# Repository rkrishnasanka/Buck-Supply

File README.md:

# Buck Supply

## Buck Design Parameters

| Parameter             | Value |
|-----------------------|-------|
| Buck Inductor         | TBD   |
| Bootstrap Capacitance | TBD   |
| Buck Capacitor        | TBD   |

- Maximum input voltage is determined by the VCC for the NE555 and the IRS2004.
- The Bootstrap Capacitor has to have a small value to allow for a quick charge.
- The Buck Capacitor has to be large enough to absorb the entire voltage ripple at the output.

## Amplifier Design Parameters

- The amplifier gain (hence the magnitude of the error) is determined by the values of R1, R2, R3, R4.
- The gain should be such that the input to the comparator is good.

## Current Source Design Parameters

- By adjusting the R1, R2, RE we can adjust the value of the current source.
- Use the resources to figure out how to design the current source.

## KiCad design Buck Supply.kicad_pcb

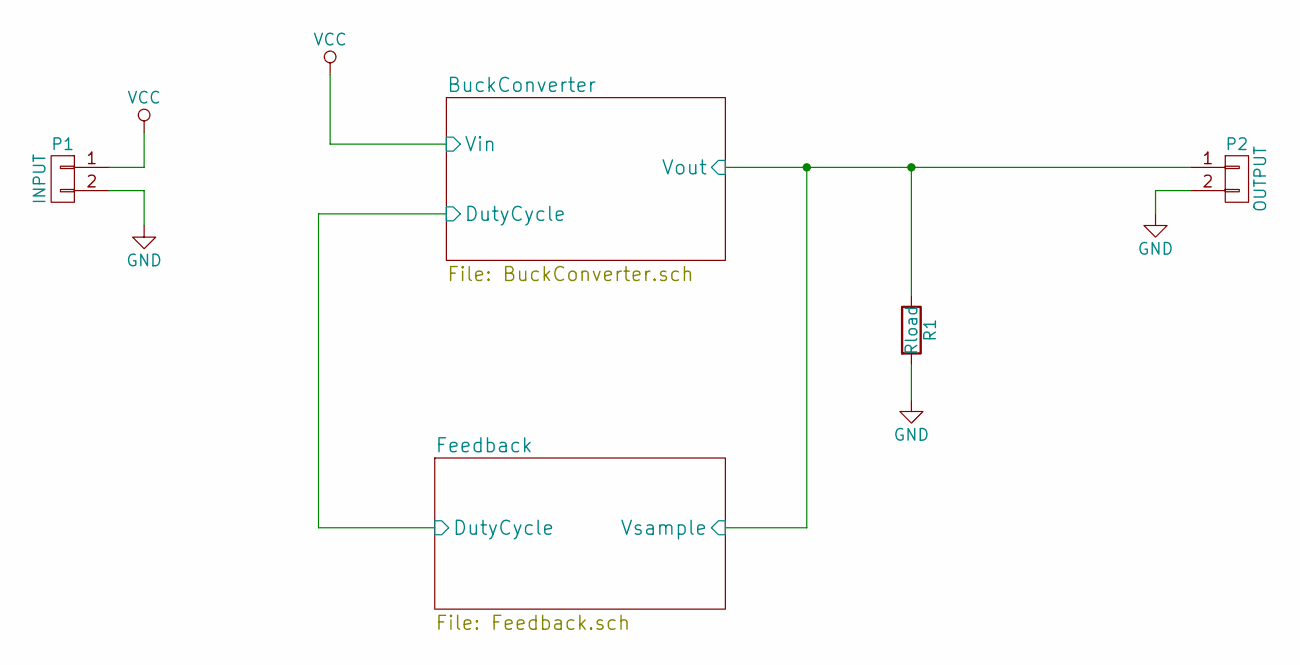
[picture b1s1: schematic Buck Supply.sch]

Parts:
P1: INPUT; Banana_Jack_2Pin
P2: OUTPUT; Banana_Jack_2Pin
R1: Rload; Resistor_Horizontal_RM30mm

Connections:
/BuckConverter/Vout: P2.1, R1.1; also elsewhere on the board
GND: P1.2, P2.2, R1.2; also elsewhere on the board
VCC: P1.1; also elsewhere on the board

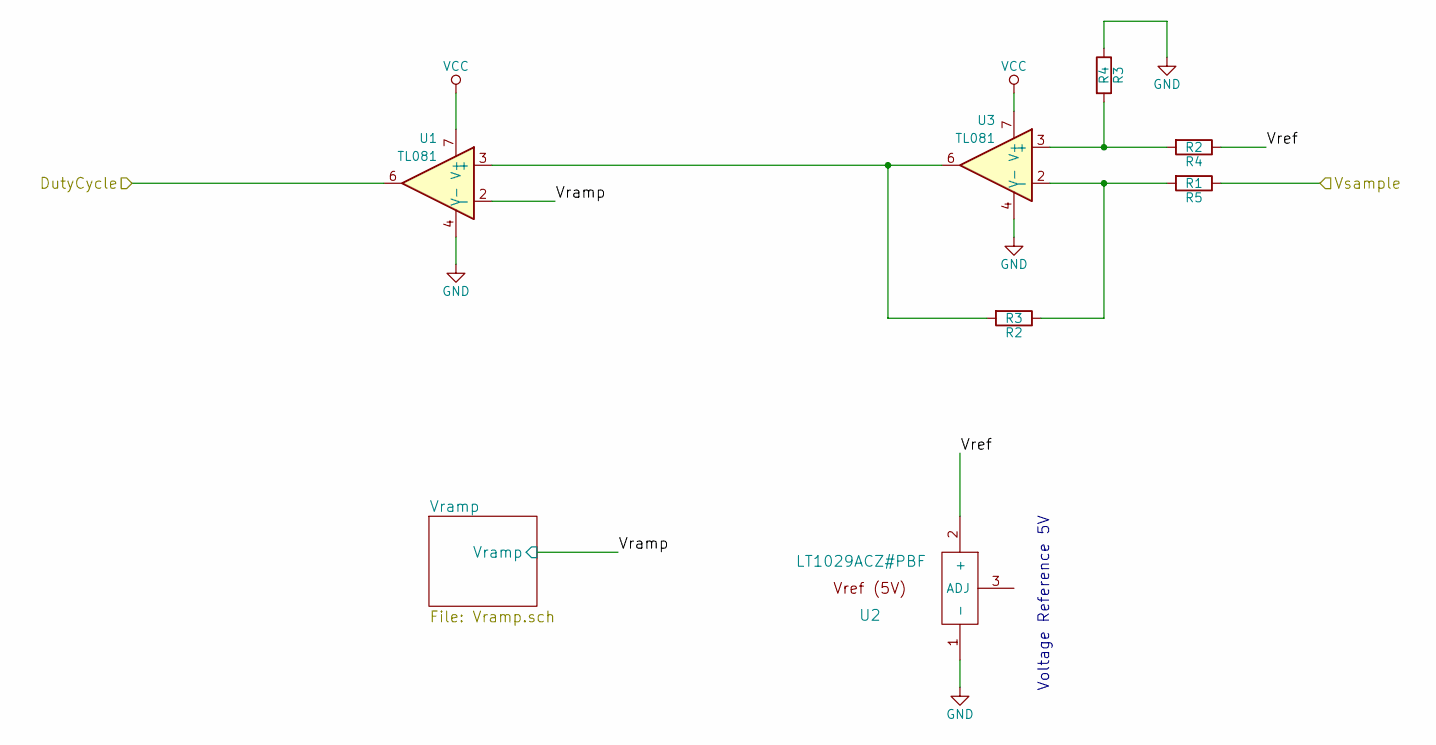
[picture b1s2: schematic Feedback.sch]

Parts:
R2: R3; Resistor_Horizontal_RM7mm
R3: R4; Resistor_Horizontal_RM7mm
R4: R2; Resistor_Horizontal_RM7mm
R5: R1; Resistor_Horizontal_RM7mm
U1, U3: TL081; DIP-8_W7.62mm_LongPads
U2: LT1029ACZ#PBF; TO-92_Inline_Wide

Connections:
/BuckConverter/DutyCycle: U1.6; also elsewhere on the board
/BuckConverter/Vout: R5.1; also elsewhere on the board
/Feedback/Vramp: U1.2 (-); also elsewhere on the board
/Feedback/Vref: R4.1, U2.2 (+)
GND: R3.1, U1.4 (V-), U2.1 (-), U3.4 (V-); also elsewhere on the board
unnamed: R2.1, R5.2, U3.2 (-)
unnamed: R2.2, U1.3 (+), U3.6
unnamed: R3.2, R4.2, U3.3 (+)
VCC: U1.7 (V+), U3.7 (V+); also elsewhere on the board

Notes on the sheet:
Voltage Reference 5V

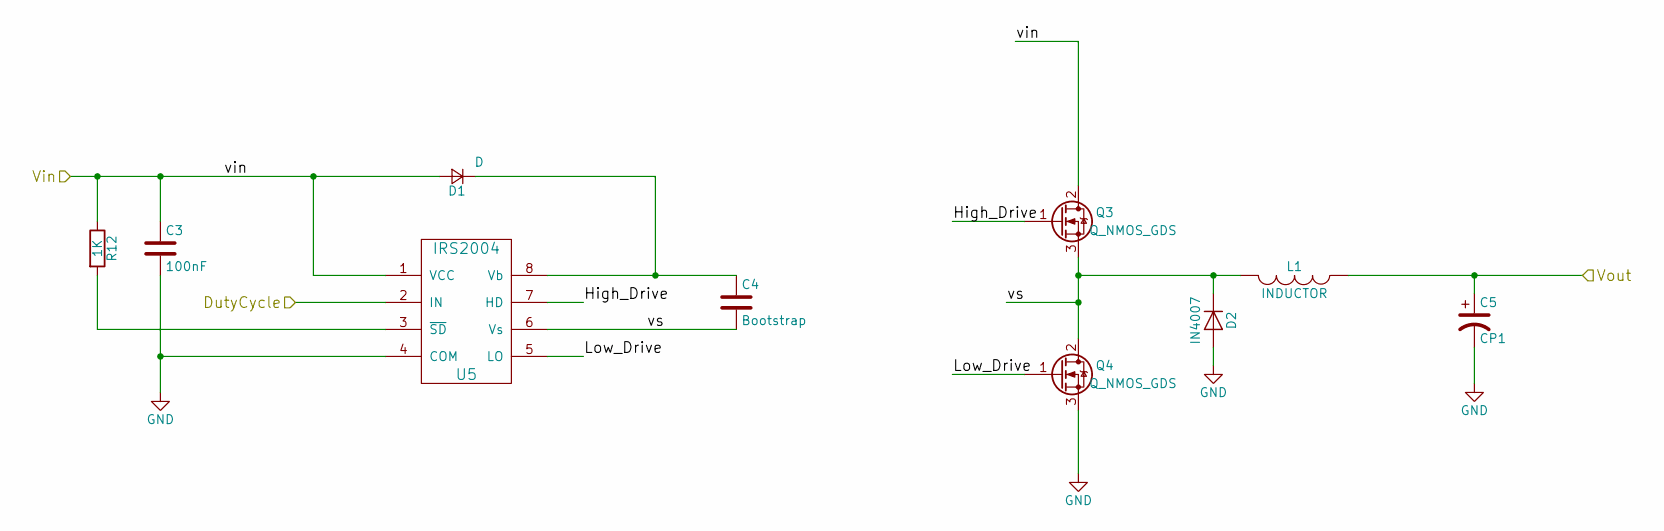
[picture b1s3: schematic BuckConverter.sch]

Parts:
C3: 100nF; C_Disc_D3_P2.5
C4: Bootstrap; C_Disc_D3_P2.5
C5: CP1; C_Radial_D16_L30_P7.5
D1: D; Diode_DO-35_SOD27_Horizontal_RM10
D2: IN4007; Diode_DO-41_SOD81_Horizontal_RM10
L1: INDUCTOR; Neosid_Inductor_Sd75
Q3, Q4: Q_NMOS_GDS; TO-220_Neutral123_Horizontal
R12: 1K; Resistor_Horizontal_RM7mm
U5: IRS2004; DIP-8_W7.62mm_LongPads

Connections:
/BuckConverter/DutyCycle: U5.2 (IN); also elsewhere on the board
/BuckConverter/High_Drive: Q3.1 (G), U5.7 (HD)
/BuckConverter/Low_Drive: Q4.1 (G), U5.5 (LO)
/BuckConverter/Vout: C5.1, L1.1; also elsewhere on the board
/BuckConverter/vs: C4.2, D2.1 (K), L1.2, Q3.3 (S), Q4.2 (D), U5.6 (Vs)
GND: C3.2, C5.2, D2.2 (A), Q4.3 (S), U5.4 (COM); also elsewhere on the board
unnamed: C4.1, D1.1 (K), U5.8 (Vb)
unnamed: R12.2, U5.3 (~SD)
VCC: C3.1, D1.2 (A), Q3.2 (D), R12.1, U5.1 (VCC); also elsewhere on the board

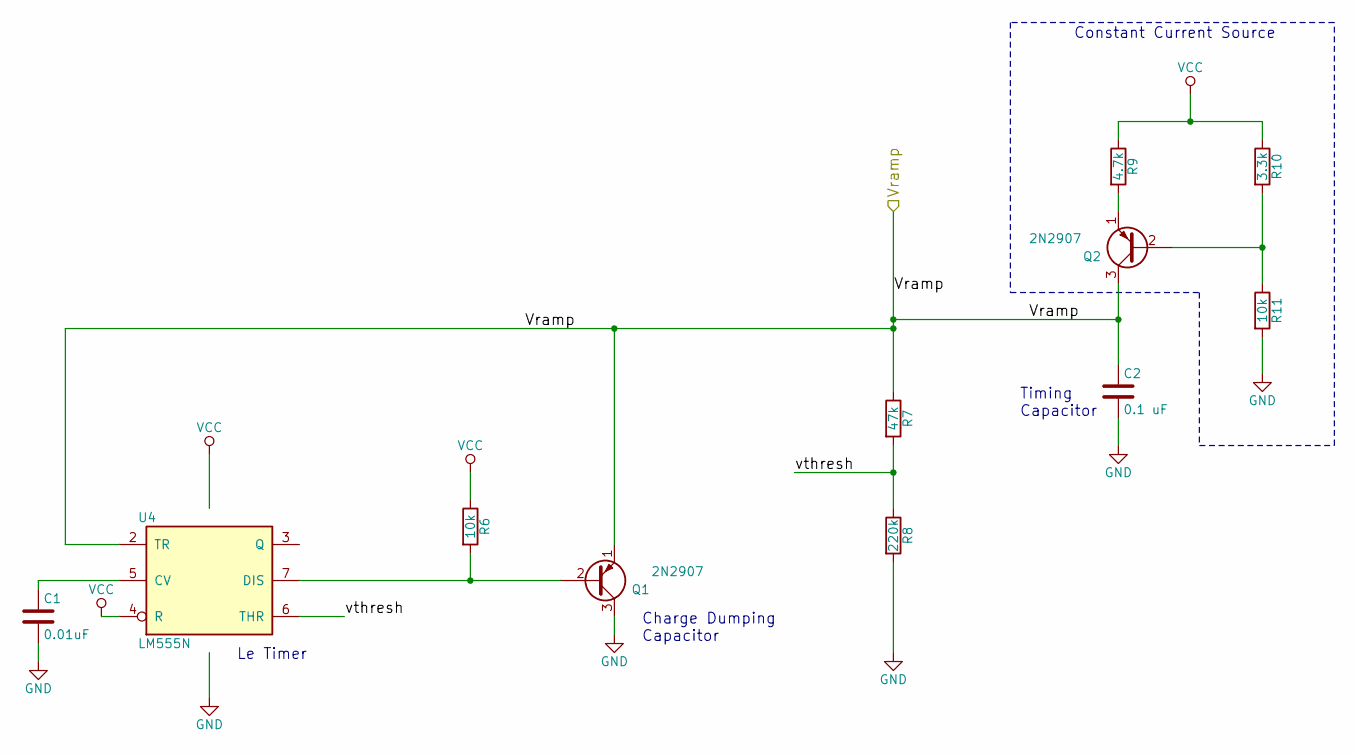
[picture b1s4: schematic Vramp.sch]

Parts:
C1: 0.01uF; C_Disc_D3_P2.5
C2: 0.1 uF; C_Disc_D3_P2.5
Q1, Q2: 2N2907; TO-18_3Pin
R6, R11: 10k; Resistor_Horizontal_RM7mm
R7: 47k; Resistor_Horizontal_RM7mm
R8: 220k; Resistor_Horizontal_RM7mm
R9: 4.7k; Resistor_Horizontal_RM7mm
R10: 3.3k; Resistor_Horizontal_RM7mm
U4: LM555N; DIP-8_W7.62mm_LongPads

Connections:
/Feedback/Vramp: C2.1, Q1.1 (E), Q2.3 (C), R7.1, U4.2 (TR); also elsewhere on the board
/Feedback/Vramp/vthresh: R7.2, R8.1, U4.6 (THR)
GND: C1.2, C2.2, Q1.3 (C), R8.2, R11.2, U4.1 (GND); also elsewhere on the board
unnamed: C1.1, U4.5 (CV)
unnamed: Q1.2 (B), R6.2, U4.7 (DIS)
unnamed: Q2.1 (E), R9.2
unnamed: Q2.2 (B), R10.2, R11.1
VCC: R6.1, R9.1, R10.1, U4.4 (R), U4.8 (VCC); also elsewhere on the board

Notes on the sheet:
Constant Current Source
Timing Capacitor
Le Timer
Charge Dumping Capacitor

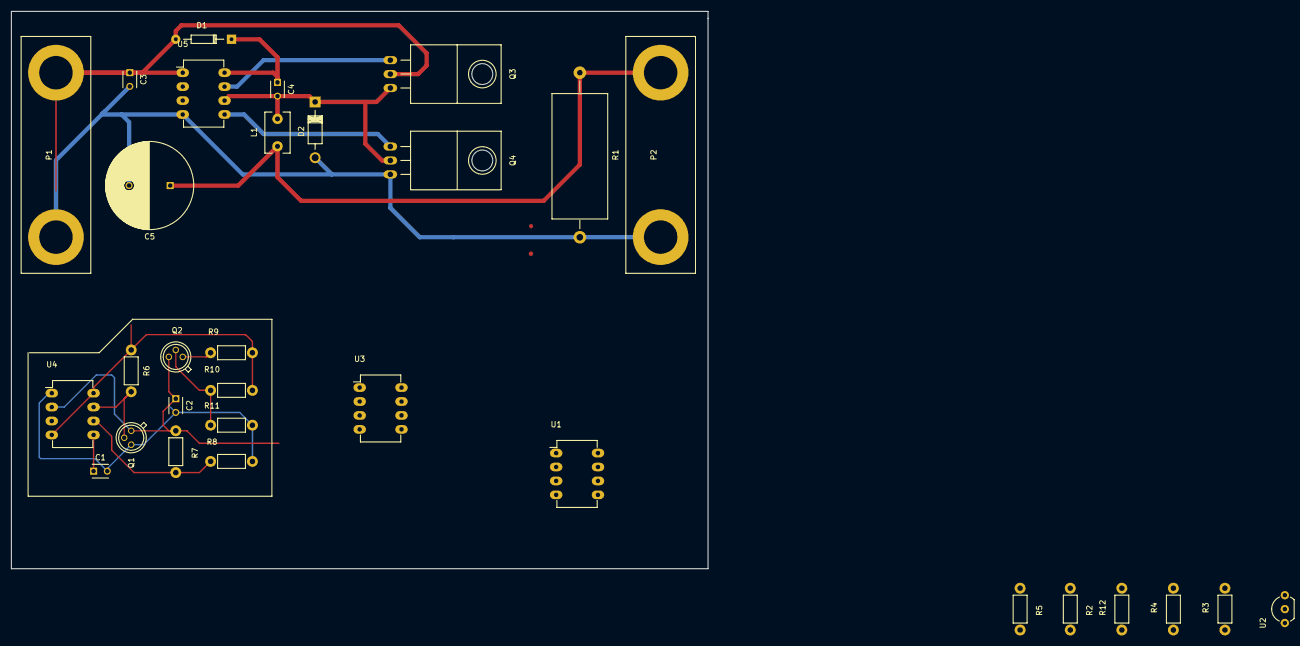
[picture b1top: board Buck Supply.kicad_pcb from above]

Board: 2 copper layers, 127.0 x 101.6 mm, 31 parts (0 on the bottom side), 19 nets.

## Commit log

2017-03-01 :tada: Added .gitattributes
2017-03-01 Added the basic Buck Schematic with the IRL2004
2017-03-01 Created Ramp Voltage Source
2017-03-01 Added some text to make things more obvious
2017-03-01 Added the Opamp Datasheet
2017-03-02 Added both the timer chip and readme
2017-03-02 Finished the full circuit.
    All thats left is to set the design parameters.
2017-03-05 Did a whole bunch of layout
2017-04-05 Updated Resources and Datasheets
